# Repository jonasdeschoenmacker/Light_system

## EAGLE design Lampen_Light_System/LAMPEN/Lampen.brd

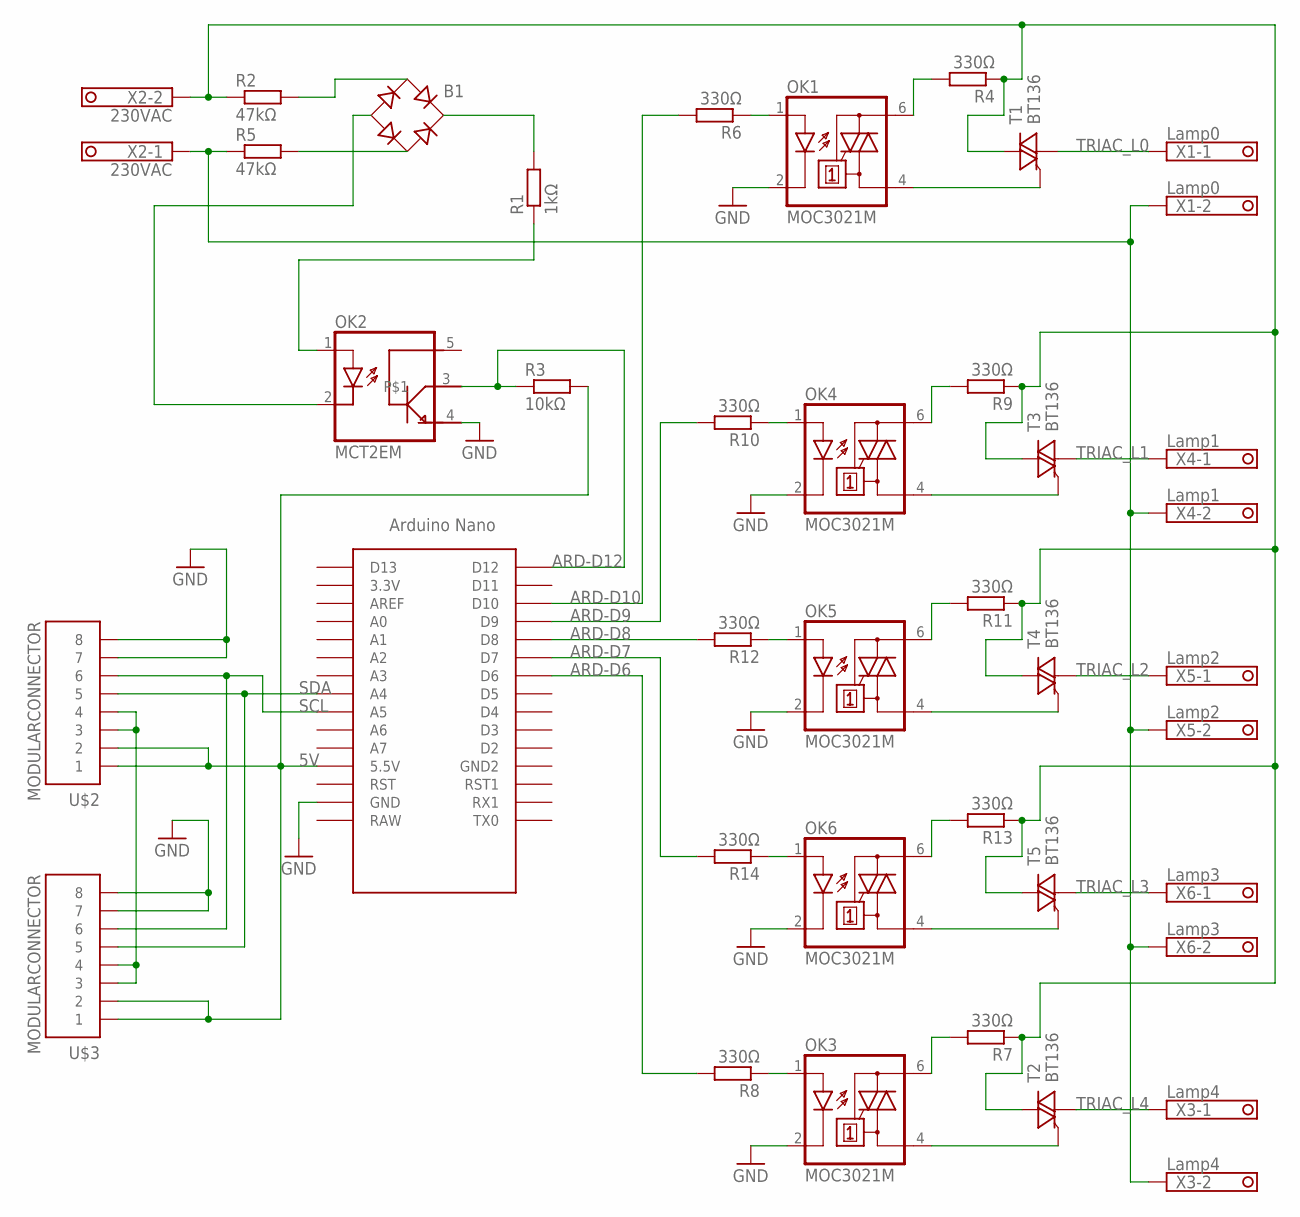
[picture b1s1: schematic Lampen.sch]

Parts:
B1: B250C1500G; RB1A
OK1, OK3, OK4, OK5, OK6: MOC3021M; DIL06
OK2: MCT2EM; DIL06
R1: 1kΩ; M1206
R2, R5: 47kΩ; R2512
R3: 10kΩ; M1206
R4, R6, R7, R8, R9, R10, R11, R12, R13, R14: 330Ω; M1206
T1, T2, T3, T4, T5: BT136; TO220DS
U$1: NANO
U$2, U$3: MODULARCONNECTOR; MA04-2
X1: Lamp0; 1751248
X2: 230VAC; 1751248
X3: Lamp4; 1751248
X4: Lamp1; 1751248
X5: Lamp2; 1751248
X6: Lamp3; 1751248

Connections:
3.3V: U$2.3, U$2.4, U$3.3, U$3.4
5V: R3.2, U$1.5V (5.5V), U$2.1, U$2.2, U$3.1, U$3.2
230VL: R2.1, R4.1, R7.1, R9.1, R11.1, R13.1, T1.A2, T2.A2, T3.A2, T4.A2, T5.A2, X2.2
230VN: R5.1, X1.2, X2.1, X3.2, X4.2, X5.2, X6.2
ARD-D6: R8.2, U$1.D6
ARD-D7: R14.2, U$1.D7
ARD-D8: R12.2, U$1.D8
ARD-D9: R10.2, U$1.D9
ARD-D10: R6.2, U$1.D10
ARD-D12: OK2.3, R3.1, U$1.D12
GND: OK1.2 (C), OK2.4 (A1), OK3.2 (C), OK4.2 (C), OK5.2 (C), OK6.2 (C), U$1.GND, U$2.7, U$2.8, U$3.7, U$3.8
unnamed: B1.AC2, R5.2
unnamed: B1.+, R1.2
unnamed: OK2.1 (A), R1.1
unnamed: B1.AC1, R2.2
unnamed: OK1.1 (A), R6.1
unnamed: B1.-, OK2.2 (C)
unnamed: OK1.4 (A1), T1.G
unnamed: OK1.6 (A2), R4.2
unnamed: OK4.4 (A1), T3.G
unnamed: OK3.4 (A1), T2.G
unnamed: OK3.6 (A2), R7.2
unnamed: OK3.1 (A), R8.1
unnamed: OK4.6 (A2), R9.2
unnamed: OK4.1 (A), R10.1
unnamed: OK5.4 (A1), T4.G
unnamed: OK5.6 (A2), R11.2
unnamed: OK5.1 (A), R12.1
unnamed: OK6.4 (A1), T5.G
unnamed: OK6.6 (A2), R13.2
unnamed: OK6.1 (A), R14.1
SCL: U$1.A5, U$2.6, U$3.6
SDA: U$1.A4, U$2.5, U$3.5
TRIAC_L0: T1.A1, X1.1
TRIAC_L1: T3.A1, X4.1
TRIAC_L2: T4.A1, X5.1
TRIAC_L3: T5.A1, X6.1
TRIAC_L4: T2.A1, X3.1

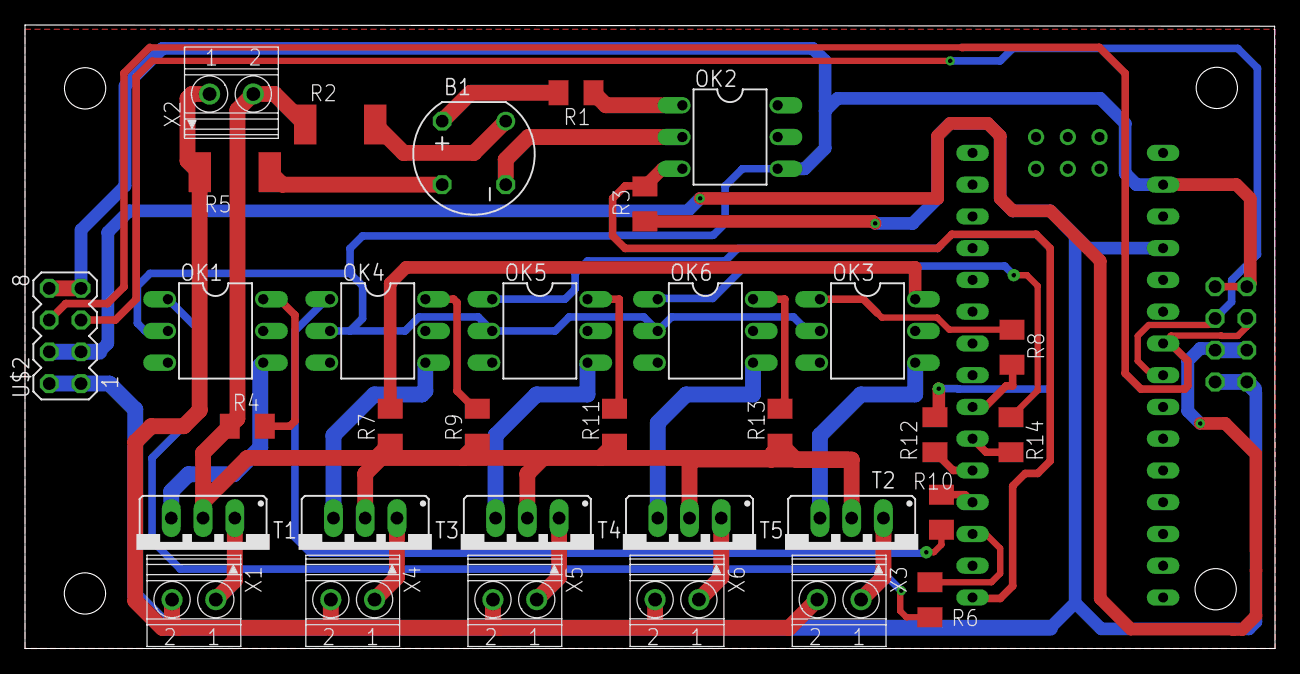
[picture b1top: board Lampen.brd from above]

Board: 2 copper layers, 100.0 x 49.9 mm, 35 parts (1 on the bottom side), 38 nets.

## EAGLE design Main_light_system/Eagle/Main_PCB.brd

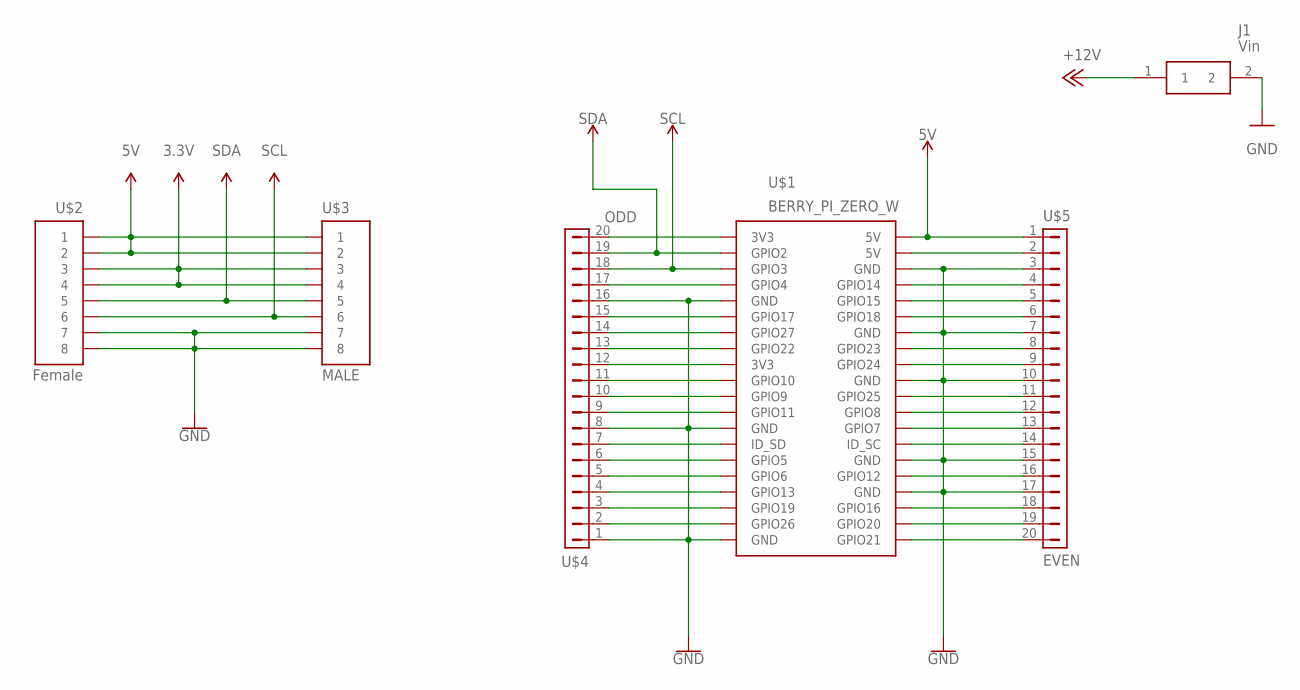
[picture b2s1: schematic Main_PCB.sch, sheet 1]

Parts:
J1: Vin; 1990009
U$1: BERRY_PI_ZERO_W; FE20-2
U$2: Female; MA04-2
U$3: MALE; MA04-2
U$4: ODD; FE20
U$5: EVEN; FE20

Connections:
3.3V: U$2.3, U$2.4, U$3.3, U$3.4; also elsewhere on the board
5V: U$1.2 (5V), U$2.1, U$2.2, U$3.1, U$3.2, U$5.1; also elsewhere on the board
5V@2: U$1.4 (5V), U$5.2
+12V: J1.1; also elsewhere on the board
GND: J1.2, U$1.6 (GND), U$1.9 (GND), U$1.14 (GND), U$1.20 (GND), U$1.25 (GND), U$1.30 (GND), U$1.34 (GND), U$1.39 (GND), U$2.7, U$2.8, U$3.7, U$3.8, U$4.1, U$4.8, U$4.16, U$5.3, U$5.7, U$5.10, U$5.15, U$5.17; also elsewhere on the board
unnamed: U$1.1 (3V3), U$4.20
unnamed: U$1.37 (GPIO26), U$4.2
unnamed: U$1.35 (GPIO19), U$4.3
unnamed: U$1.33 (GPIO13), U$4.4
unnamed: U$1.31 (GPIO6), U$4.5
unnamed: U$1.29 (GPIO5), U$4.6
unnamed: U$1.27 (ID_SD), U$4.7
unnamed: U$1.17 (3V3), U$4.12
unnamed: U$1.23 (GPIO11), U$4.9
unnamed: U$1.21 (GPIO9), U$4.10
unnamed: U$1.19 (GPIO10), U$4.11
unnamed: U$1.15 (GPIO22), U$4.13
unnamed: U$1.13 (GPIO27), U$4.14
unnamed: U$1.11 (GPIO17), U$4.15
unnamed: U$1.7 (GPIO4), U$4.17
unnamed: U$1.8 (GPIO14), U$5.4
unnamed: U$1.10 (GPIO15), U$5.5
unnamed: U$1.12 (GPIO18), U$5.6
unnamed: U$1.16 (GPIO23), U$5.8
unnamed: U$1.18 (GPIO24), U$5.9
unnamed: U$1.22 (GPIO25), U$5.11
unnamed: U$1.24 (GPIO8), U$5.12
unnamed: U$1.26 (GPIO7), U$5.13
unnamed: U$1.28 (ID_SC), U$5.14
unnamed: U$1.32 (GPIO12), U$5.16
unnamed: U$1.36 (GPIO16), U$5.18
unnamed: U$1.38 (GPIO20), U$5.19
unnamed: U$1.40 (GPIO21), U$5.20
SCL: U$1.5 (GPIO3), U$2.6, U$3.6, U$4.18
SDA: U$1.3 (GPIO2), U$2.5, U$3.5, U$4.19

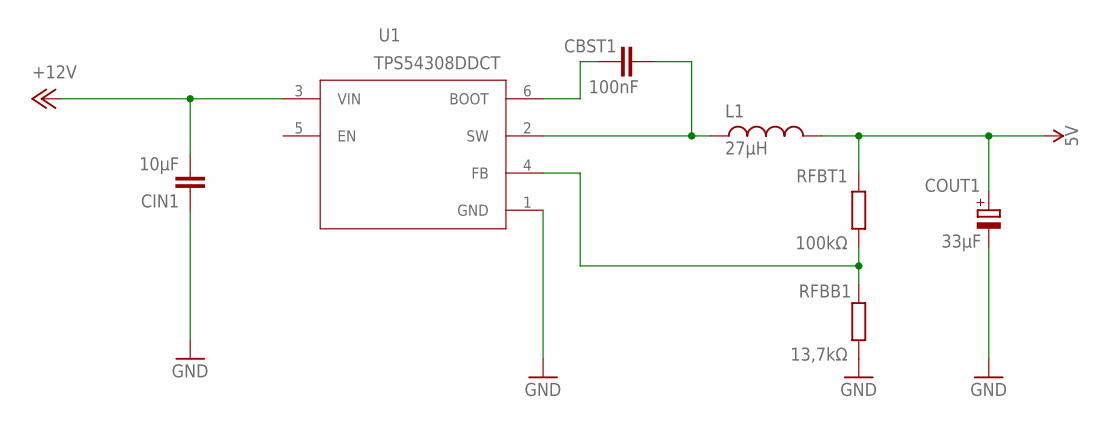
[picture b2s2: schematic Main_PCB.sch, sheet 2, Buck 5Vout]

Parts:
CBST1: 100nF; C0603
CIN1: 10µF; C1210
COUT1: 33µF; PANASONIC_C
L1: 27µH; WE-PDF
RFBB1: 13,7kΩ; R0603
RFBT1: 100kΩ; R0805
U1: TPS54308DDCT; DDC6

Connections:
5V: COUT1.+, L1.2, RFBT1.2; also elsewhere on the board
+12V: CIN1.2, U1.3 (VIN); also elsewhere on the board
GND: CIN1.1, COUT1.-, RFBB1.1, U1.1 (GND); also elsewhere on the board
unnamed: CBST1.2, L1.1, U1.2 (SW)
unnamed: CBST1.1, U1.6 (BOOT)
unnamed: RFBB1.2, RFBT1.1, U1.4 (FB)

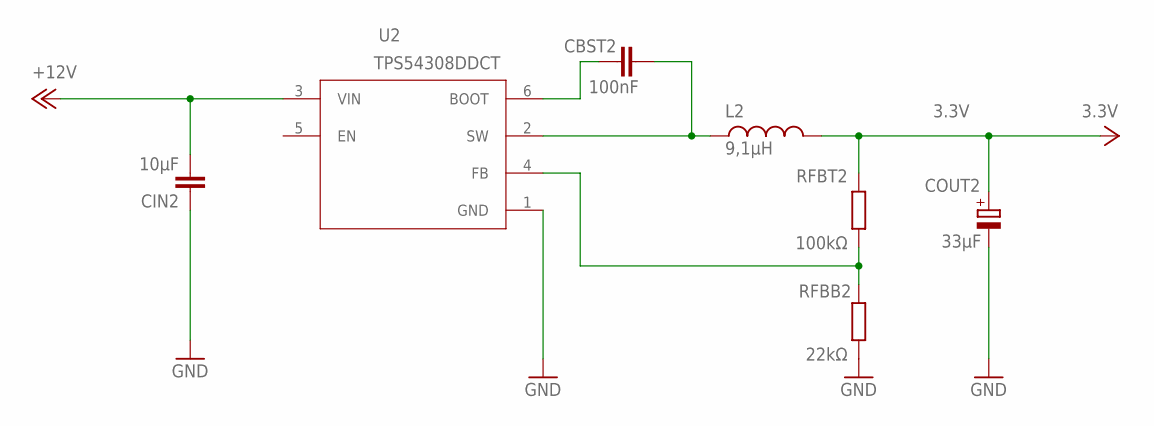
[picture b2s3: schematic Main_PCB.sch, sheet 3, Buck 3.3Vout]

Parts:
CBST2: 100nF; C0603
CIN2: 10µF; C1210
COUT2: 33µF; PANASONIC_C
L2: 9,1µH; WE-PDF
RFBB2: 22kΩ; R0603
RFBT2: 100kΩ; R0805
U2: TPS54308DDCT; DDC6

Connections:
3.3V: COUT2.+, L2.2, RFBT2.2; also elsewhere on the board
+12V: CIN2.2, U2.3 (VIN); also elsewhere on the board
GND: CIN2.1, COUT2.-, RFBB2.1, U2.1 (GND); also elsewhere on the board
unnamed: CBST2.2, L2.1, U2.2 (SW)
unnamed: CBST2.1, U2.6 (BOOT)
unnamed: RFBB2.2, RFBT2.1, U2.4 (FB)

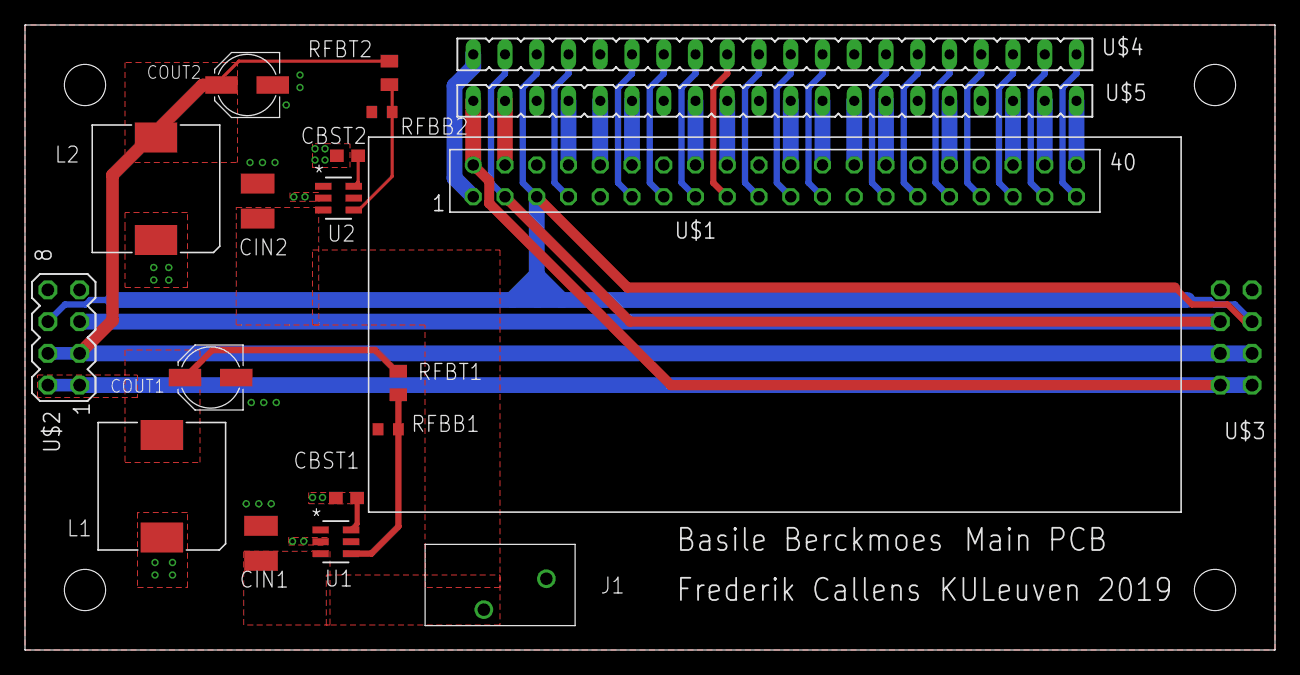
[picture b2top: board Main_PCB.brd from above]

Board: 2 copper layers, 100.0 x 50.0 mm, 20 parts (1 on the bottom side), 41 nets.

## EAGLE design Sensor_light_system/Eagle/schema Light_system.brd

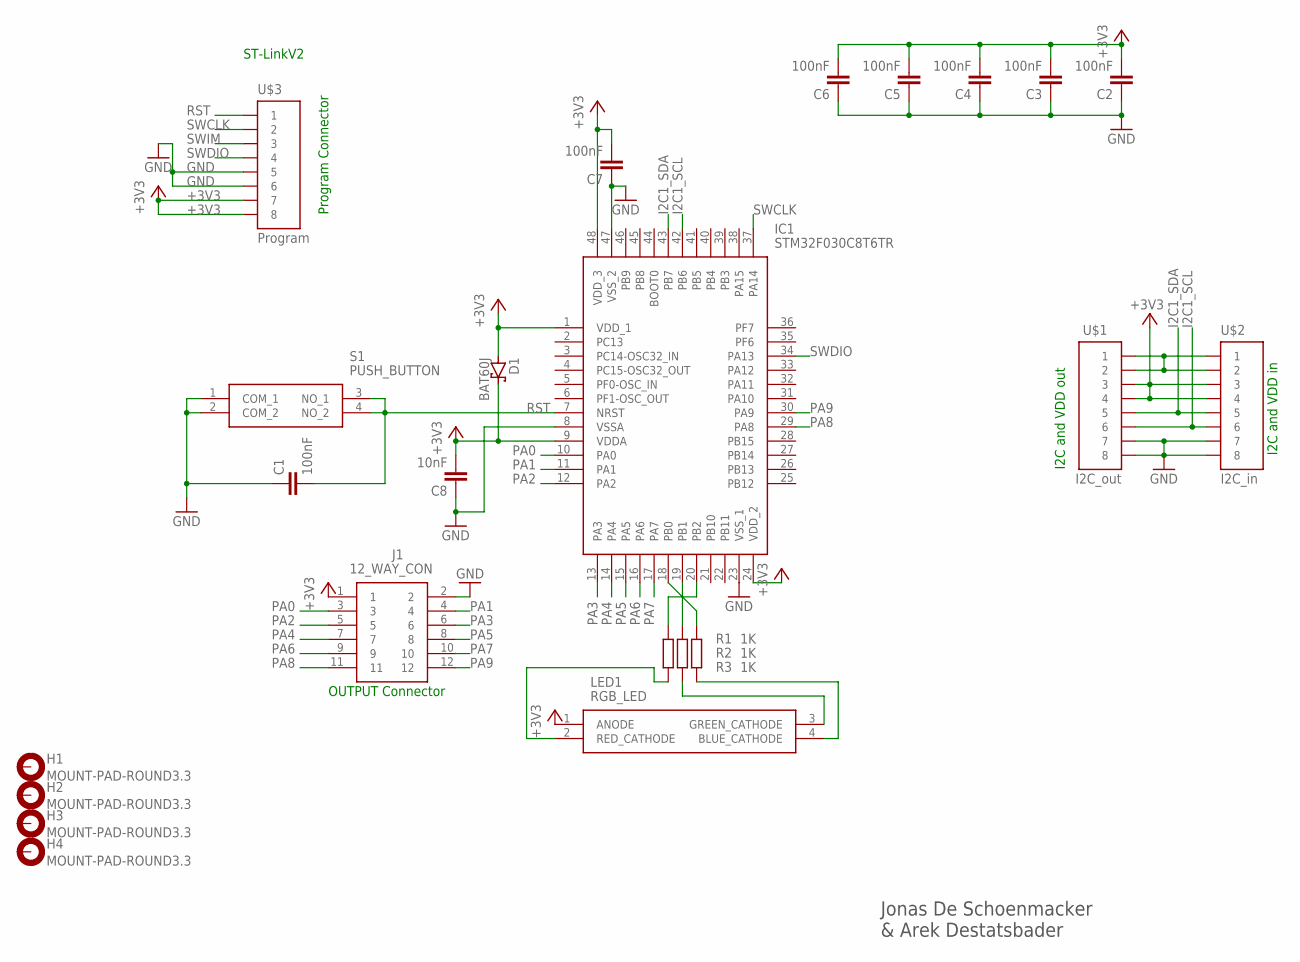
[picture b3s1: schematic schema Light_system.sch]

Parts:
C1, C2, C3, C4, C5, C6, C7: 100nF; C1206
C8: 10nF; C1206
D1: BAT60J; SOD323_ST
H1, H2, H3, H4: MOUNT-PAD-ROUND3.3; 3,3-PAD
IC1: STM32F030C8T6TR; QFP50P900X900X160-48N
J1: 12_WAY_CON; 1990106
LED1: RGB_LED; ASMBKTF00A306
R1, R2, R3: 1K; R1206
S1: PUSH_BUTTON; LL3301FF065QJ
U$1: I2C_out; MA04-2
U$2: I2C_in; MA04-2
U$3: Program; MA04-2

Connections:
+3V3: C2.2, C3.2, C4.2, C5.2, C6.2, C7.2, C8.2, D1.A, D1.C, IC1.1 (VDD_1), IC1.9 (VDDA), IC1.24 (VDD_2), IC1.48 (VDD_3), J1.1, LED1.1 (ANODE), U$1.3, U$1.4, U$2.3, U$2.4, U$3.7, U$3.8
GND: C1.1, C2.1, C3.1, C4.1, C5.1, C6.1, C7.1, C8.1, IC1.8 (VSSA), IC1.23 (VSS_1), IC1.47 (VSS_2), J1.2, S1.1 (COM_1), S1.2 (COM_2), U$1.7, U$1.8, U$2.7, U$2.8, U$3.5, U$3.6
I2C1_SCL: IC1.42 (PB6), U$1.6, U$2.6
I2C1_SDA: IC1.43 (PB7), U$1.5, U$2.5
unnamed: LED1.2 (RED_CATHODE), R1.1
unnamed: LED1.3 (GREEN_CATHODE), R2.1
unnamed: IC1.20 (PB2), R1.2
unnamed: LED1.4 (BLUE_CATHODE), R3.1
unnamed: U$1.1, U$1.2, U$2.1, U$2.2
unnamed: IC1.19 (PB1), R2.2
unnamed: IC1.18 (PB0), R3.2
PA0: IC1.10 (PA0), J1.3
PA1: IC1.11 (PA1), J1.4
PA2: IC1.12 (PA2), J1.5
PA3: IC1.13 (PA3), J1.6
PA4: IC1.14 (PA4), J1.7
PA5: IC1.15 (PA5), J1.8
PA6: IC1.16 (PA6), J1.9
PA7: IC1.17 (PA7), J1.10
PA8: IC1.29 (PA8), J1.11
PA9: IC1.30 (PA9), J1.12
RST: C1.2, IC1.7 (NRST), S1.3 (NO_1), S1.4 (NO_2), U$3.1
SWCLK: IC1.37 (PA14), U$3.2
SWDIO: IC1.34 (PA13), U$3.4
SWIM: U$3.3

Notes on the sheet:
Jonas De Schoenmacker & Arek Destatsbader
Program Connector
I2C and VDD in
I2C and VDD out
OUTPUT Connector
ST-LinkV2

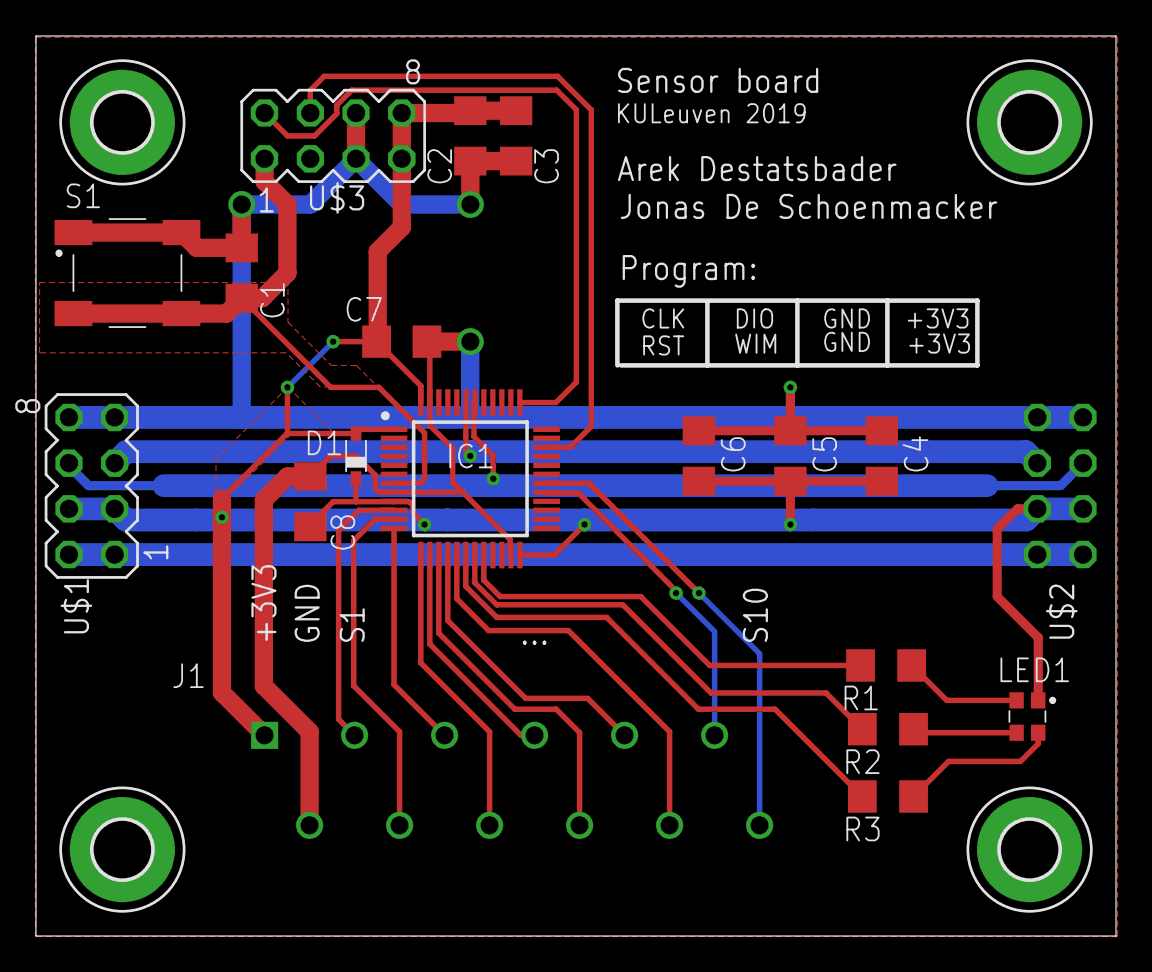
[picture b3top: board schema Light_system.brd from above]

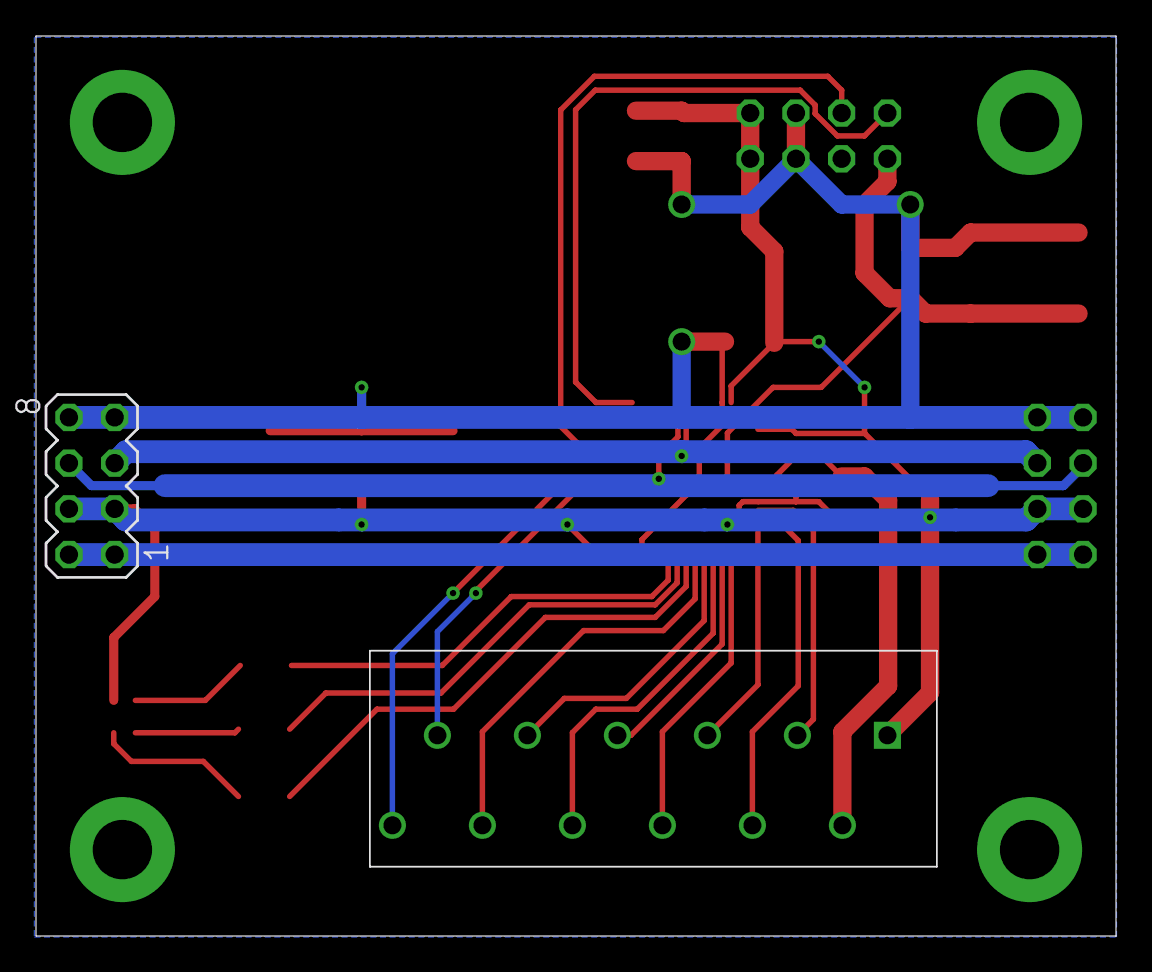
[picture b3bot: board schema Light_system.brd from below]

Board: 2 copper layers, 60.0 x 50.0 mm, 23 parts (2 on the bottom side), 24 nets.

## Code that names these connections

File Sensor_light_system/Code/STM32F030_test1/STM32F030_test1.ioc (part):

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Mcu.Name=STM32F030C8Tx
Mcu.Package=LQFP48
Mcu.UserName=STM32F030C8Tx
PA0.Signal=GPIO_Input
PA1.Signal=GPIO_Input
PA13.Mode=Serial_Wire
PA13.Signal=SYS_SWDIO
PA14.Mode=Serial_Wire
PA14.Signal=SYS_SWCLK
PA2.Signal=GPIO_Input
PA3.Signal=GPIO_Input
PA4.Signal=GPIO_Input
PA5.Signal=GPIO_Input
PA6.Signal=GPIO_Input
PA7.Signal=GPIO_Input
PA8.Signal=GPIO_Input
PA9.Signal=GPIO_Input
PB0.Signal=GPIO_Output
PB1.Signal=GPIO_Output
PB2.Signal=GPIO_Output
PB6.Mode=I2C
PB6.Signal=I2C1_SCL
PB7.Mode=I2C
PB7.Signal=I2C1_SDA
board=custom

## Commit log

2019-09-30 Added Sensor folder
2019-09-30 BOM added
2019-09-30 BOM updated sensor
2019-10-02 BOM and datasheets update
2019-10-02 Eagle file added
2019-10-05 bom update
    main pcb
2019-10-05 Update BOM Light_system.xlsx
    main pcb bom 3.3buck
2019-10-05 Schema bucks & bom update
2019-10-05 update main pcb
2019-10-14 BOM changed, components added
2019-10-14 BOM changed
2019-10-14 Libr added
2019-10-14 U MA = U PA
2019-10-14 Je verneukt het weer
2019-10-14 Schema sensor changed
2019-10-14 schema sensor aangepast
2019-10-14 Main lib aangepast
2019-10-14 Niel is gay
2019-10-14 main pcb update
2019-10-14 schema sensoren
2019-10-14 Folder code added
2019-10-14 schema main update
2019-10-14 test project Added
2019-10-14 schema sensor
2019-10-14 schema sensor gewijzigd
2019-10-14 NIEL is omo
2019-10-20 schema Light_system
2019-10-28 schema gewijziged
2019-10-28 Afmetingen toegevoegd
2019-10-28 PCB Afmetingen update
2019-10-28 board aangepast
2019-10-28 eagle
2019-10-28 code aangepast
2019-10-28 eagel
2019-10-28 main.c sensor aangepast
2019-10-28 PCB Main bijna af
2019-11-16 File opkuis 1
2019-11-16 pcb main af?
2019-11-18 gerbers
2019-11-18 gerbers update
2019-11-18 file update
2019-11-18 opgave toegevoegd
2019-11-18 sensor bijgewerkt
2019-11-18 gerbers sensor gemaakt
2019-11-19 unrar
2019-11-19 gerbers final
2019-11-19 stls
2019-11-23 pcb update
2019-11-24 laatste aanpassing
2019-11-25 gerber files sensor updated
2019-11-25 laatste aanpassingen
2019-11-25 gerbers r2order
2019-12-02 stl's
2019-12-02 bom check
2019-12-02 ds store verwijderd
2019-12-02 files verwijderd
2019-12-02 code sensor added
2019-12-02 V1 added
2019-12-11 versie_11_12_19_V2 code added
2019-12-11 update versie_11_12_19_V2 code
2019-12-12 code upload
2019-12-13 code 13/12 added
2019-12-15 update versie_13_12_19_V2 code
2019-12-16 final push git
2019-12-19 toevoegen code main light system

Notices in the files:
parts and their libraries:
SparkFun-PowerSymbols: Licensing: Creative Commons ShareAlike 4.0 International - https://creativecommons.org/licenses/by-sa/4.0
